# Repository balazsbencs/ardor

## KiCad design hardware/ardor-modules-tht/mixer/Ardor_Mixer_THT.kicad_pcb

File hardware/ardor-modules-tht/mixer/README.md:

# Stereo buffer / mono average / AC outputs / HAND ASSEMBLY

T1.1 compact hand-assembly PCB: 70 × 48 mm. **Unbuilt engineering prototype.**

[KiCad project](Ardor_Mixer_THT.kicad_pro) · [Manual BOM](BOM.csv) · [Schematic](review/schematic.pdf) · [Bare-board Gerbers](assembly/Ardor_Mixer_THT-Gerbers.zip)

Supply 5 V / 10 mA. Fit **MCP6022-I/P** DIP-8 amplifiers; TLV9002 SOIC parts from M1 do not fit. Use **Nichicon UES1H100MPM, 10 µF / 50 V bipolar**, for C401/C402/C407/C408/C409. The 3.5 mm-pitch footprints reserve the manufacturer's maximum 8.5 mm body diameter; maximum can height is 12.5 mm. Either orientation is valid. C101 and C403 are ordinary polarized radial capacitors, positive on pad 1.

Inputs are line-level, no greater than 1 Vrms per channel. Outputs drive loads of at least 10 kΩ. OUT_MONO is `(LEFT + RIGHT) / 2`; all three outputs are AC-coupled. Feeding only one channel gives half its amplitude at the mono output. Feed both channels for a full-level mono source. The board is not an instrument preamp or headphone amplifier.

Commission with no signal: check the filtered 5 V rail and about 2.5 V at VREF and the internal buffer outputs. Check near-zero settled DC on the external outputs. Feed separate 1 kHz left/right tones and verify unity stereo buffers, mono averaging and channel separation. Check clipping, noise and oscillation across the audio band. Keep external harnesses short; exposed audio sockets need entry protection.

## Connector pin assignments

Directions are relative to this board. Standard header square pads identify pin 1. Read reference and pin numbers from the back silkscreen; mirrored CAD exports are labelled as back views.

### J101 — 5V POWER INPUT

| Pin | Net | Direction | Connect to |
|---|---|---|---|
| 1 | +5V | POWER INPUT | Positive output of the matching regulated supply. |
| 2 | GND | GROUND | Host or cable ground / 0 V. |

### J102 — STEREO AUDIO INPUT FROM SOURCE

| Pin | Net | Direction | Connect to |
|---|---|---|---|
| 1 | AUDIO_L | INPUT | DAC/codec left audio output, <=1 Vrms. |
| 2 | GND | GROUND | Host or cable ground / 0 V. |
| 3 | AUDIO_R | INPUT | DAC/codec right audio output, <=1 Vrms. |

### J103 — BUFFERED STEREO + MONO AUDIO OUTPUT

| Pin | Net | Direction | Connect to |
|---|---|---|---|
| 1 | OUT_L | OUTPUT | Left line input of another device, >=10k load. |
| 2 | GND | GROUND | Host or cable ground / 0 V. |
| 3 | OUT_R | OUTPUT | Right line input of another device, >=10k load. |
| 4 | OUT_MONO | OUTPUT | Mono line input, >=10k load. Signal is (L+R)/2. |

## Assembly and files

Fit low-profile axial parts first, then sockets/headers and radial capacitors. Match diode bands, electrolytic polarity and IC notches to the PCB. Install the ICs or ADC breakout last. H1/H2 are 2.2 mm nonplated M2 mounting holes, not electrical terminals. Check enclosure clearance and capacitor/socket height. T1.1 compacts the layouts; hole positions differ from T1 and M1.

Use the manual BOM and the bare-board Gerber/drill ZIP. There is no SMT assembly order. Front silkscreen shows component references; the front fabrication drawing shows package outlines and orientation; use the BOM for values. Back silk includes port functions and pin numbers. Native checks and package manifests are under `verification/`; they do not replace prototype measurements.

[Assembly accessories](assembly/accessories.csv) list sockets, shunts and panel items in addition to the PCB component BOM.

[Family guide](../README.md) · [Substitution sources](../SOURCES.md) · [Native validation](verification/validation.json)

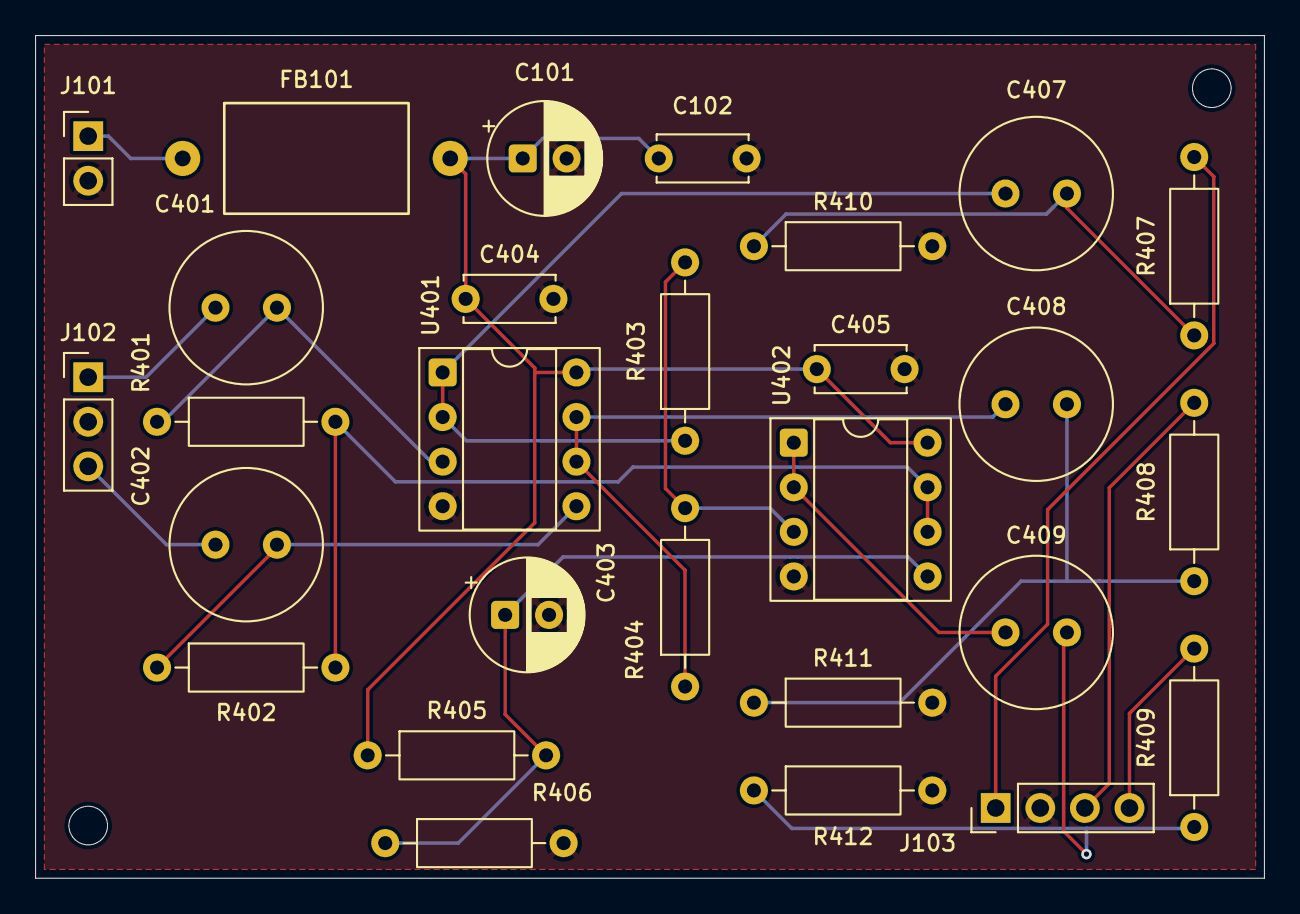
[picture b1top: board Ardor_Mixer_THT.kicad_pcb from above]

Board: 2 copper layers, 70.0 x 48.0 mm, 30 parts (0 on the bottom side), 19 nets.

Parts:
C101: 22u / 25V polarized; CP_Radial_D6.3mm_P2.50mm
C102, C404, C405: 100n / 50V X7R; C_Disc_D5.0mm_W2.5mm_P5.00mm
C401, C402, C407, C408, C409: 10u / 50V BIPOLAR; CP_Bipolar_Nichicon_D8.0mm_P3.50mm
C403: 10u / 25V polarized; CP_Radial_D6.3mm_P2.50mm
FB101: 800R@100MHz / WE 7427501; Ferrite_WE_7427501_P15.24mm
H1, H2: MountingHole_2.2mm_M2
J101: 5V POWER INPUT; PinHeader_1x02_P2.54mm_Vertical
J102: STEREO AUDIO INPUT FROM SOURCE; PinHeader_1x03_P2.54mm_Vertical
J103: BUFFERED STEREO + MONO AUDIO OUTPUT; PinHeader_1x04_P2.54mm_Vertical
R401, R402, R410, R411, R412: 100kR / 1% 0.25W; R_Axial_DIN0207_L6.3mm_D2.5mm_P10.16mm_Horizontal
R403, R404, R405, R406: 10kR / 1% 0.25W; R_Axial_DIN0207_L6.3mm_D2.5mm_P10.16mm_Horizontal
R407, R408, R409: 100R / 1% 0.25W; R_Axial_DIN0207_L6.3mm_D2.5mm_P10.16mm_Horizontal
U401, U402: MCP6022-I/P; DIP-8_W7.62mm_Socket

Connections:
/+5V: FB101.1, J101.1
/+5V_A: C101.1, C102.1, C404.1, C405.1, FB101.2, R405.1, U401.8, U402.8
/GND: C101.2, C102.2, C403.2, C404.2, C405.2, J101.2, J102.2, J103.2, R406.2, R410.2, R411.2, R412.2, U401.4, U402.4
/VREF: R401.2, R402.2, U402.6, U402.7
unnamed: C407.2, R407.1, R410.1
unnamed: C408.2, R408.1, R411.1
unnamed: C409.2, R409.1, R412.1
unnamed: C401.1, J102.1
unnamed: C402.1, J102.3
unnamed: J103.1, R407.2
unnamed: J103.3, R408.2
unnamed: J103.4, R409.2
unnamed: C401.2, R401.1, U401.3
unnamed: C407.1, R403.1, U401.1, U401.2
unnamed: C402.2, R402.1, U401.5
unnamed: C408.1, R404.1, U401.6, U401.7
unnamed: R403.2, R404.2, U402.3
unnamed: C409.1, U402.1, U402.2
unnamed: C403.1, R405.2, R406.1, U402.5

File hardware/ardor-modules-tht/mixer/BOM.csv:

Reference,Value,Footprint,Purchasing specification,Assembly
J102,STEREO AUDIO INPUT FROM SOURCE,Connector_PinHeader_2.54mm:PinHeader_1x03_P2.54mm_Vertical,PinHeader_1x03_P2.54mm_Vertical,THT manual
J101,5V POWER INPUT,Connector_PinHeader_2.54mm:PinHeader_1x02_P2.54mm_Vertical,PinHeader_1x02_P2.54mm_Vertical,THT manual
J103,"BUFFERED STEREO + MONO AUDIO
OUTPUT",Connector_PinHeader_2.54mm:PinHeader_1x04_P2.54mm_Vertical,PinHeader_1x04_P2.54mm_Vertical,THT manual
FB101,800R@100MHz / WE 7427501,Ardor_THT:Ferrite_WE_7427501_P15.24mm,Wurth Elektronik 7427501,THT manual
C101,22u / 25V polarized,Capacitor_THT:CP_Radial_D6.3mm_P2.50mm,"Radial electrolytic 22uF 25V, D<=6.3mm P2.5mm",THT manual
C102,100n / 50V X7R,Capacitor_THT:C_Disc_D5.0mm_W2.5mm_P5.00mm,"100nF 50V X7R radial, 5mm lead pitch",THT manual
C401,10u / 50V BIPOLAR,Ardor_THT:CP_Bipolar_Nichicon_D8.0mm_P3.50mm,Nichicon UES1H100MPM (HESTORE 100.524.69),THT manual
R401,100kR / 1% 0.25W,Resistor_THT:R_Axial_DIN0207_L6.3mm_D2.5mm_P10.16mm_Horizontal,Axial metal film 100kΩ 1% 0.25W,THT manual
U401,MCP6022-I/P,Package_DIP:DIP-8_W7.62mm_Socket,Microchip MCP6022-I/P,THT manual
R403,10kR / 1% 0.25W,Resistor_THT:R_Axial_DIN0207_L6.3mm_D2.5mm_P10.16mm_Horizontal,Axial metal film 10kΩ 1% 0.25W,THT manual
C402,10u / 50V BIPOLAR,Ardor_THT:CP_Bipolar_Nichicon_D8.0mm_P3.50mm,Nichicon UES1H100MPM (HESTORE 100.524.69),THT manual
R402,100kR / 1% 0.25W,Resistor_THT:R_Axial_DIN0207_L6.3mm_D2.5mm_P10.16mm_Horizontal,Axial metal film 100kΩ 1% 0.25W,THT manual
R404,10kR / 1% 0.25W,Resistor_THT:R_Axial_DIN0207_L6.3mm_D2.5mm_P10.16mm_Horizontal,Axial metal film 10kΩ 1% 0.25W,THT manual
U402,MCP6022-I/P,Package_DIP:DIP-8_W7.62mm_Socket,Microchip MCP6022-I/P,THT manual
C407,10u / 50V BIPOLAR,Ardor_THT:CP_Bipolar_Nichicon_D8.0mm_P3.50mm,Nichicon UES1H100MPM (HESTORE 100.524.69),THT manual
R407,100R / 1% 0.25W,Resistor_THT:R_Axial_DIN0207_L6.3mm_D2.5mm_P10.16mm_Horizontal,Axial metal film 100Ω 1% 0.25W,THT manual
R410,100kR / 1% 0.25W,Resistor_THT:R_Axial_DIN0207_L6.3mm_D2.5mm_P10.16mm_Horizontal,Axial metal film 100kΩ 1% 0.25W,THT manual
C408,10u / 50V BIPOLAR,Ardor_THT:CP_Bipolar_Nichicon_D8.0mm_P3.50mm,Nichicon UES1H100MPM (HESTORE 100.524.69),THT manual
R408,100R / 1% 0.25W,Resistor_THT:R_Axial_DIN0207_L6.3mm_D2.5mm_P10.16mm_Horizontal,Axial metal film 100Ω 1% 0.25W,THT manual
R411,100kR / 1% 0.25W,Resistor_THT:R_Axial_DIN0207_L6.3mm_D2.5mm_P10.16mm_Horizontal,Axial metal film 100kΩ 1% 0.25W,THT manual
C409,10u / 50V BIPOLAR,Ardor_THT:CP_Bipolar_Nichicon_D8.0mm_P3.50mm,Nichicon UES1H100MPM (HESTORE 100.524.69),THT manual
R409,100R / 1% 0.25W,Resistor_THT:R_Axial_DIN0207_L6.3mm_D2.5mm_P10.16mm_Horizontal,Axial metal film 100Ω 1% 0.25W,THT manual
R412,100kR / 1% 0.25W,Resistor_THT:R_Axial_DIN0207_L6.3mm_D2.5mm_P10.16mm_Horizontal,Axial metal film 100kΩ 1% 0.25W,THT manual
R405,10kR / 1% 0.25W,Resistor_THT:R_Axial_DIN0207_L6.3mm_D2.5mm_P10.16mm_Horizontal,Axial metal film 10kΩ 1% 0.25W,THT manual
R406,10kR / 1% 0.25W,Resistor_THT:R_Axial_DIN0207_L6.3mm_D2.5mm_P10.16mm_Horizontal,Axial metal film 10kΩ 1% 0.25W,THT manual
C403,10u / 25V polarized,Capacitor_THT:CP_Radial_D6.3mm_P2.50mm,"Radial electrolytic 10uF 25V, D<=6.3mm P2.5mm",THT manual
C404,100n / 50V X7R,Capacitor_THT:C_Disc_D5.0mm_W2.5mm_P5.00mm,"100nF 50V X7R radial, 5mm lead pitch",THT manual
C405,100n / 50V X7R,Capacitor_THT:C_Disc_D5.0mm_W2.5mm_P5.00mm,"100nF 50V X7R radial, 5mm lead pitch",THT manual

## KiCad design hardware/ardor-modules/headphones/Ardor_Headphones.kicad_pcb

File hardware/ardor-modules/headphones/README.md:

# Ardor Optional stereo headphones — M1

An external stereo line-level source feeds the local TPA6132A2 and charge pump. No mixer or external negative supply is required.

Power from an external regulated **5 V / 50 mA** supply budget. These figures reserve operating margin; they are not measured consumption. No onboard input regulator or reverse-power protection is provided. Use only the named rails and connect host GND. Budget each fitted module separately.

[Single-page schematic](review/schematic.pdf) · [Component placement](review/pcb-assembly.svg) · [Front routing](review/pcb-front.svg) · [Back routing and connector legends](review/pcb-back.svg)

[Short assembly guide](ASSEMBLY.md) · [Beginner pin card](review/wiring-guide.pdf)

## Connector pins

All connectors/jumpers are 2.54 mm headers. **Square pad = pin 1.** Pin numbers below are native schematic/PCB numbers, not left-to-right screen positions. Back-side text is read from the back of the physical board. The same reference names appear on multiple modules; use this board’s table. **J101 pin assignments differ between module types; harnesses are not interchangeable.**

| Connector | Pin | Direction / function | Connect to |
|---|---|---|---|
| J101 | 1 | **POWER INPUT** — Feed regulated 5V into the module. This pin does not supply power. | Positive output of the matching regulated supply. |
| J101 | 2 | **GROUND** — Common 0 V return; not a signal or positive supply. | Host or cable ground / 0 V. |
| J101 | 3 | **CONTROL INPUT** — 3.3 V HIGH = on; 0 V LOW or disconnected = off. | Host control output. Keep LOW until audio and supply are stable. |
| J102 | 1 | **INPUT** — LEFT audio enters the module. | DAC/codec left audio output, <=1 Vrms. |
| J102 | 2 | **GROUND** — Common 0 V return; not a signal or positive supply. | Host or cable ground / 0 V. |
| J102 | 3 | **INPUT** — RIGHT audio enters the module. | DAC/codec right audio output, <=1 Vrms. |
| J602 | 1 | **OUTPUT** — LEFT audio leaves the module. | TRS socket tip; headphones >=32 ohm. |
| J602 | 2 | **OUTPUT** — RIGHT audio leaves the module. | TRS socket ring; headphones >=32 ohm. |
| J602 | 3 | **GROUND** — Common 0 V return; not a signal or positive supply. | TRS socket sleeve; enclosure bond. |

**IN** enters this board. **OUT** leaves this board. **I/O** uses both directions. **GND** is the common 0 V return. **3V3** means 3.3 V.

H1/H2 are mounting holes. Small via holes and other component pads are not wire connectors.

## Wiring and commissioning

Connect an external stereo line-level DAC/codec to J102: pin 1 left, pin 2 ground, pin 3 right; each **≤1 Vrms**. J602 goes to a TRS headphone socket: pin 1 tip/left, pin 2 ring/right, pin 3 sleeve/GND. The sleeve/bushing bonds the enclosure through the local CHASSIS/GND link. Use headphones of **32 Ω or greater**; there is no balanced output.

J101 pin 3 **HP_ENABLE** is a 3.3 V logic input. LOW or disconnected disables the amplifier; HIGH enables it. Keep it low until audio and 5 V are stable, then start at low volume and ramp up. Do not drive enable above the amplifier’s supply plus 0.3 V when unpowered. Both gain pins are grounded, selecting **−6 dB inverting gain**. A 1 Vrms input gives about 0.47 Vrms / 6.8 mW per channel into 32 Ω after the 2.2 Ω output resistors (nominal calculation, not a measured result).

The TPA6132A2 charge-pump flying/storage capacitors, exposed-pad ground and input DC blocking are all local. HPVDD/HPVSS are internal rails and must not be connected to external power. This module deliberately carries the optional QFN amplifier and its added assembly/X-ray cost so other features do not pay for it. The local 0.5 mm pitch QFN land and 0.2 mm drilled thermal vias are frozen in this project; do not substitute a generic footprint in an ordering copy.

Fit J101/J102/J602 by hand. SMT includes U601 and the charge-pump capacitors. Inspect U601 pin 1 and exposed-pad soldering in the JLCPCB preview and delivered boards. Bring-up into resistive dummy loads first: check supplies, enable operation, channel assignment, output DC, charge-pump ripple, clipping/noise and hot-plug behavior. Then test headphones at low volume.

## Order this board

Upload [the fabrication ZIP](assembly/Ardor_Headphones-JLCPCB-Gerbers.zip), [SMT BOM](assembly/jlcpcb-bom.csv) and [CPL](assembly/jlcpcb-cpl.csv) as **one separate design**. Select two assembled boards, two copper layers, 1.6 mm FR-4, 1 oz finished copper, and top-side SMT assembly only. The ZIP includes both silk/mask/copper layers and separate PTH/NPTH drill files. Use the supplied absolute origin throughout; do not apply an auxiliary-origin shift to just the CPL.

The dated parts/loss model is **$9.93** for two boards, plus **$12.28** for 4 Economic Extended feeder types, plus approximately $3.28 QFN X-ray. This excludes PCB/setup/stencil/joints/shipping/tax/manual parts and is not a checkout quote. Public stock was checked **2 October 2026**; no parts are reserved. Recheck the exact C-codes and quantities when ordering.

[Manual-fit BOM](assembly/manual-bom.csv) lists headers. Panel sockets, wires, host, regulated supply, M2 hardware and enclosure are external items, chosen to suit the build; they are not in the SMT order. This PCB has two 2.2 mm NPTH mounting holes. Keep conductive mounting hardware clear of copper.

Inspect **every IC, diode and polarized capacitor** against its pin 1/polarity in JLCPCB’s interactive placement preview. CPL uses native KiCad CCW angles; the supplier may assign a different zero orientation for its part model. That preview has not been checked or approved here. Correct supplier-side rotations before paying.

[Verification summary](verification/validation.json) records clean ERC/DRC/parity, physical pad/net checks, uniform widths and zero inter-module dependencies. These are design checks; the M1 boards have not been built or bench-tested. Complete the commissioning checks above before treating them as validated hardware.

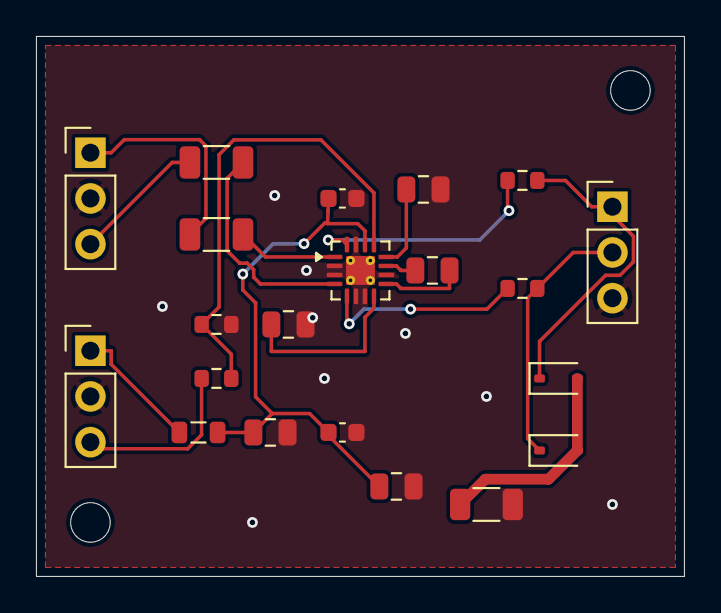
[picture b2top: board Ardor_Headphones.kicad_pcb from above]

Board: 2 copper layers, 36.0 x 30.0 mm, 23 parts (0 on the bottom side), 18 nets.

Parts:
C101: 22u / 25V X5R; C_0805_2012Metric
C102, C604: 100n / 50V X7R; C_0603_1608Metric
C601, C602: 10u / 50V X5R; C_1206_3216Metric
C603, C605, C606, C607: 2.2u / 25V X7R; C_0805_2012Metric
D601, D602: PESD5V0S1BA,115; D_SOD-323
FB101: 600R@100MHz; L_0805_2012Metric
H1, H2: MountingHole_2.2mm_M2
J101: 5V POWER + ENABLE INPUT; PinHeader_1x03_P2.54mm_Vertical
J102: STEREO AUDIO INPUT FROM SOURCE; PinHeader_1x03_P2.54mm_Vertical
J602: STEREO HEADPHONE AUDIO OUTPUT; PinHeader_1x03_P2.54mm_Vertical
R101: 0R / 1%; R_1206_3216Metric
R601: 1k / 1%; R_0603_1608Metric
R602: 100k / 1%; R_0603_1608Metric
R603, R604: 2.2R / 1%; R_0603_1608Metric
U601: TPA6132A2RTER; WQFN-16-1EP_3x3mm_P0.5mm_EP1.6x1.6mm_ThermalVias

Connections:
/+5V: FB101.1, J101.1
/+5V_A: C101.1, C102.1, C603.1, C604.1, FB101.2, U601.14
/CHASSIS: D601.2, D602.2, R101.1
/GND: C101.2, C102.2, C603.2, C604.2, C605.2, C606.2, J101.2, J102.2, J602.3, R101.2, R602.2, U601.2, U601.3, U601.6, U601.7, U601.10, U601.15, U601.17
/HPVDD: C605.1, U601.12
/HPVSS: C606.1, U601.8
/HP_L: D601.1, J602.1, R603.2
/HP_R: D602.1, J602.2, R604.2
unnamed: J101.3, R601.1
unnamed: C602.1, J102.1
unnamed: C601.1, J102.3
unnamed: C607.2, U601.9
unnamed: C607.1, U601.11
unnamed: R601.2, R602.1, U601.13
unnamed: C602.2, U601.1
unnamed: C601.2, U601.4
unnamed: R603.1, U601.16
unnamed: R604.1, U601.5

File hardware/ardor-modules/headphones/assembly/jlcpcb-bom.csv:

Comment,Designator,Footprint,LCSC Part #
600R@100MHz,FB101,L_0805_2012Metric,C41556732
22u / 25V X5R,C101,C_0805_2012Metric,C45783
100n / 50V X7R,"C102,C604",C_0603_1608Metric,C14663
10u / 50V X5R,"C601,C602",C_1206_3216Metric,C13585
TPA6132A2RTER,U601,WQFN-16-1EP_3x3mm_P0.5mm_EP1.6x1.6mm_ThermalVias,C69901
1k / 1%,R601,R_0603_1608Metric,C21190
100k / 1%,R602,R_0603_1608Metric,C25803
2.2R / 1%,"R603,R604",R_0603_1608Metric,C22939
"PESD5V0S1BA,115","D601,D602",D_SOD-323,C19224
0R / 1%,R101,R_1206_3216Metric,C17888
2.2u / 25V X7R,"C603,C605,C606,C607",C_0805_2012Metric,C19110

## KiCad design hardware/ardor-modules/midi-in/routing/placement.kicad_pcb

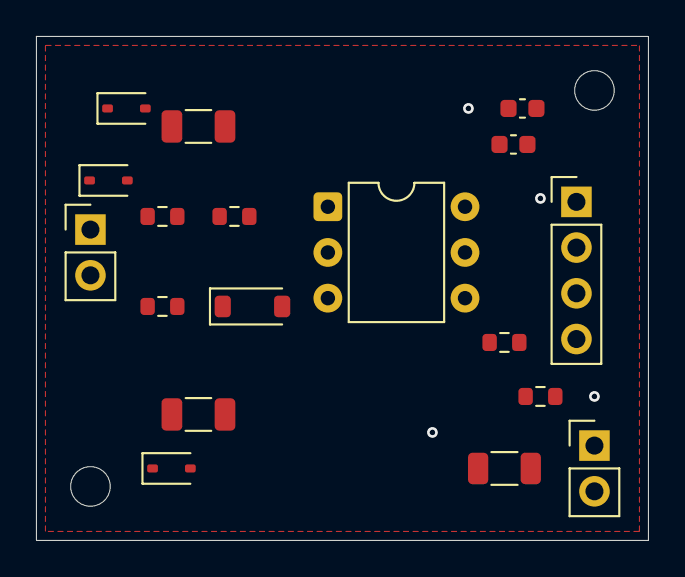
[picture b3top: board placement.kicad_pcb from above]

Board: 2 copper layers, 34.0 x 28.0 mm, 20 parts (0 on the bottom side), 11 nets, no tracks yet.

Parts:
C201, C204: 100n / 50V X7R; C_0603_1608Metric
C202, C203: TCC1206COG101J102DT; C_1206_3216Metric
D201: 1N4148W; D_SOD-123
D202: PESD5V0S1BA,115; D_SOD-323
D203, D204: PESD24VL1BA,115; D_SOD-323
FB201, FB202: 120R @100MHz; R_0603_1608Metric
H1, H2: MountingHole_2.2mm_M2
J101: +5V / +3V3 / GND / MIDI_RX; PinHeader_1x04_P2.54mm_Vertical
J202: MIDI_4 / MIDI_5; PinHeader_1x02_P2.54mm_Vertical
J203: CHASSIS / GND; PinHeader_1x02_P2.54mm_Vertical
R101: 0R / 1%; R_1206_3216Metric
R201: 220R / 1%; R_0603_1608Metric
R202: 1kR / 1%; R_0603_1608Metric
R203: 100R / 1%; R_0603_1608Metric
U201: onsemi H11L1M; DIP-6_W7.62mm

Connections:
/+3V3: C204.1, J101.2, R202.1
/+5V: C201.1, J101.1, U201.6
/CHASSIS: C202.2, C203.2, D203.2, D204.2, J203.1, R101.1
/GND: C201.2, C204.2, J101.3, J203.2, R101.2, U201.5
/MIDI_4: C202.1, D202.1, D203.1, FB201.1, J202.1
/MIDI_5: C203.1, D202.2, D204.1, FB202.1, J202.2
unnamed: D201.2, FB202.2, U201.2
unnamed: D201.1, R201.2, U201.1
unnamed: FB201.2, R201.1
unnamed: J101.4, R203.2
unnamed: R202.2, R203.1, U201.4

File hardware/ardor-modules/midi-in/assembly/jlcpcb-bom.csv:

Comment,Designator,Footprint,LCSC Part #
120R@100MHz,"FB201,FB202",R_0603_1608Metric,C14709
220R / 1%,R201,R_0603_1608Metric,C22962
1N4148W,D201,D_SOD-123,C81598
100n / 50V X7R,"C201,C204",C_0603_1608Metric,C14663
1k / 1%,R202,R_0603_1608Metric,C21190
100R / 1%,R203,R_0603_1608Metric,C22775
"PESD5V0S1BA,115",D202,D_SOD-323,C19224
100p / 1kV C0G,"C202,C203",C_1206_3216Metric,C367316
"PESD24VL1BA,115","D203,D204",D_SOD-323,C69324
0R / 1%,R101,R_1206_3216Metric,C17888
